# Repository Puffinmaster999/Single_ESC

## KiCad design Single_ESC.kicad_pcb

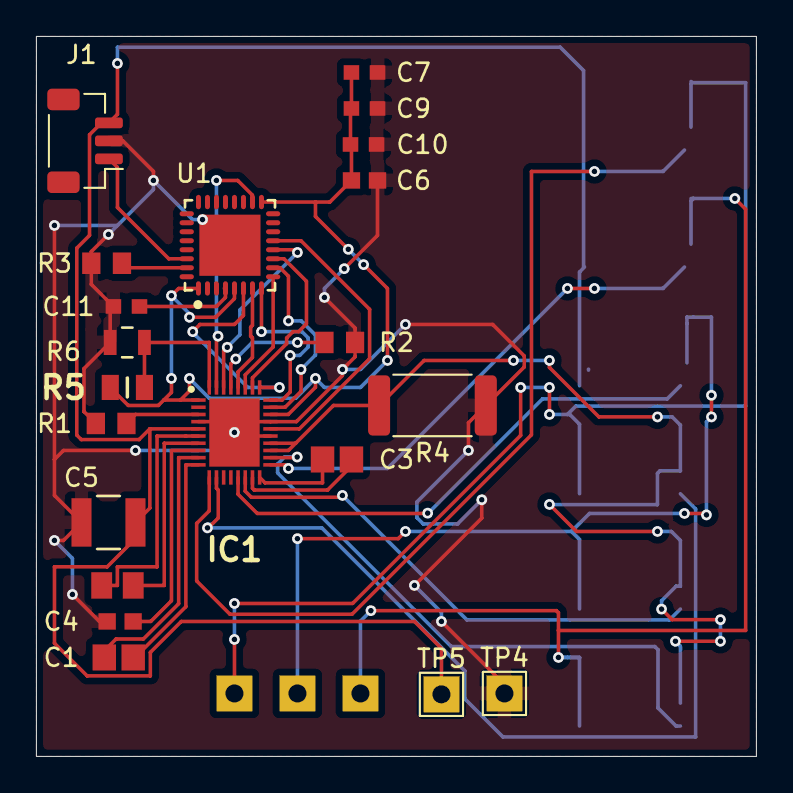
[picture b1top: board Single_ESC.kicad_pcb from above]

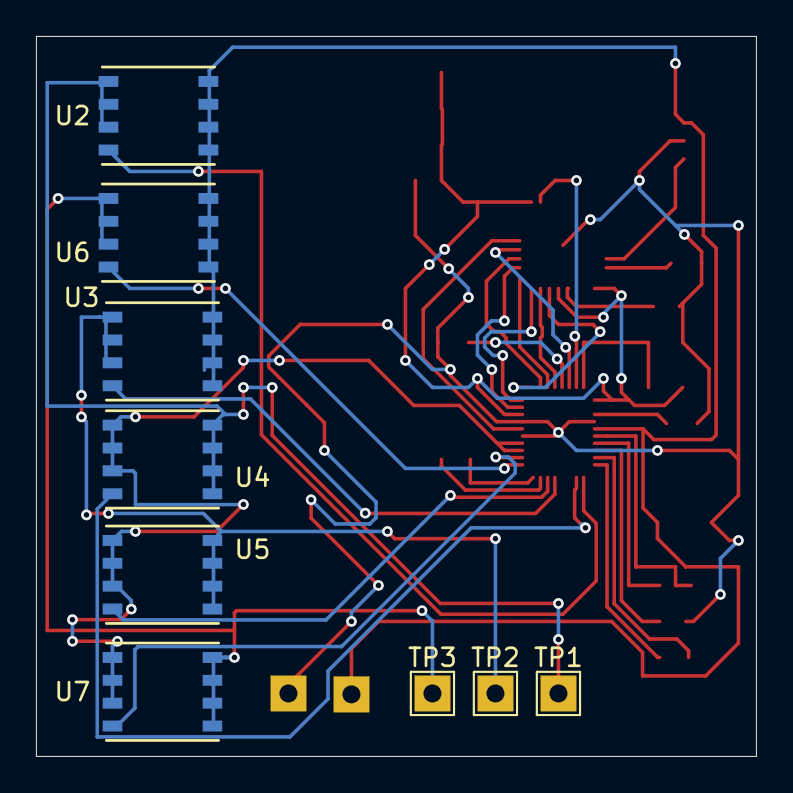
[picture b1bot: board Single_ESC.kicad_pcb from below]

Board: 2 copper layers, 40.0 x 40.0 mm, 30 parts (9 on the bottom side), 35 nets.

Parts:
C1, C3: C0805C105K5RACTU; CAPC220145_140N_KEM
C4, C6: CC0603KRX7R7BB105; YAG_CC0603_YAG
C5: CC1210KKX7R9BB106; CAP_CC1210_YAG
C7, C9, C10, C11: CC0603KRX7R7BB104; CC0603N_YAG
C8: C0805C473K5RECAUTO; CAPC2012X140N
IC1: DRV8329AREER; QFN40P400X500X80-37N-D
J1: Conn_01x03; JST_SH_BM03B-SRSS-TB_1x03-1MP_P1.00mm_Vertical
R1: RC0805JR-07100KL; RC0805N_YAG
R2: RC0805FR-07200KL; RC0805N_YAG
R3: RC0805JR-0710KL; RC0805N_YAG
R4: CRE2512-FZ-R002E-2; R_2512_6332Metric
R5: RC0805FR-0718KL; RESC2012X60N
R6: CRCW08051K00FKEA; RES_CRCW_0805
TP1, TP2, TP3, TP4, TP5: TestPoint; TestPoint_THTPad_2.0x2.0mm_Drill1.0mm
U1: AT32F421K8U7; QFN-32_L5.0-W5.0-P0.50-BL-EP3.4
U2, U3, U4, U5, U6, U7: BSC014N04LSIATMA1; PG-TDSON-8_INF

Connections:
/3V3: C6.1, C7.1, C9.1, C10.1, IC1.1 (CSAREF), IC1.26 (AVDD), R5.1, U1.1 (VDD), U1.5 (VDDA), U1.17 (VDD)
/BOOT0: R3.1, U1.31 (BOOT0)
/BSTA_1: C1.1, IC1.9 (BSTA_1)
/BSTC: C3.1, IC1.17 (BSTC)
/CPH: C8.1, IC1.7 (CPH)
/CPL: C8.2, IC1.6 (CPL)
/CSAGAIN: IC1.33 (CSAGAIN), R2.1
/DRVOFF: IC1.24 (DRVOFF), U1.13 (PA7)
/DSHOT_A: J1.1, U1.30 (PB7)
/DT: IC1.3 (DT), R1.1
/GHA: IC1.11 (GHA), U2.4 (G)
/GHB: IC1.15 (GHB), U3.4 (G)
/GHC: IC1.19 (GHC), U6.4 (G)
/GLA: IC1.12 (GLA), U4.4 (G)
/GLB: IC1.16 (GLB), U5.4 (G)
/GLC: IC1.20 (GLC), U7.4 (G)
/GND: C4.2, C5.2, C6.2, C7.2, C9.2, C10.2, C11.2, IC1.4 (GND_1), IC1.23 (SN), IC1.25 (AGND), IC1.37 (GND_2), J1.2, R1.2, R2.2, R3.2, R4.1, R6.2, TP4.1 (1_1), U1.33 (VSS)
/GVDD: C4.1, IC1.8 (GVDD)
/INHA: IC1.29 (INHA), U1.6 (PA0)
/INHB: IC1.28 (INHB), U1.8 (PA2)
/INHC: IC1.27 (INHC), U1.10 (PA4)
/INLA: IC1.32 (INLA), U1.7 (PA1)
/INLB: IC1.31 (INLB), U1.9 (PA3)
/INLC: IC1.30 (INLC), U1.11 (PA5)
/LLS: IC1.21 (LSS), IC1.22 (SP), R4.2, U4.1 (S), U4.2 (S), U4.3 (S), U5.1 (S), U5.2 (S), U5.3 (S), U7.1 (S), U7.2 (S), U7.3 (S)
/NFAULT: IC1.35 (NFAULT), U1.18 (PA8)
/NRST: C11.1, U1.4 (NRST)
/NSLEEP: IC1.34 (NSLEEP), U1.12 (PA6)
/PHASE_A: TP1.1 (1_1), U2.1 (S), U2.2 (S), U2.3 (S), U4.5 (D), U4.6 (D), U4.7 (D), U4.8 (D)
/PHASE_B: TP2.1 (1_1), U3.1 (S), U3.2 (S), U3.3 (S), U5.5 (D), U5.6 (D), U5.7 (D), U5.8 (D)
/PHASE_C: TP3.1 (1_1), U6.1 (S), U6.2 (S), U6.3 (S), U7.5 (D), U7.6 (D), U7.7 (D), U7.8 (D)
/SHA: C1.2, IC1.10 (SHA)
/SHC: C3.2, IC1.18 (SHC)
/VBAT: C5.1, IC1.5 (PVDD), J1.3, TP5.1 (1_1), U2.5 (D), U2.6 (D), U2.7 (D), U2.8 (D), U3.5 (D), U3.6 (D), U3.7 (D), U3.8 (D), U6.5 (D), U6.6 (D), U6.7 (D), U6.8 (D)
/VDSLVL: IC1.36 (VDSLVL), R5.2, R6.1
